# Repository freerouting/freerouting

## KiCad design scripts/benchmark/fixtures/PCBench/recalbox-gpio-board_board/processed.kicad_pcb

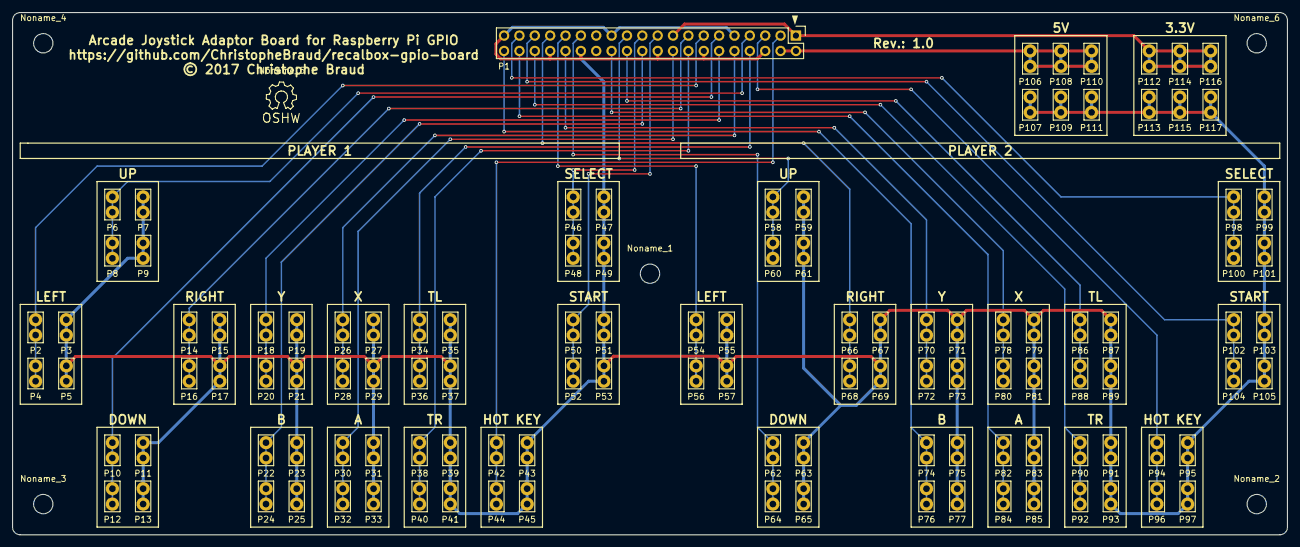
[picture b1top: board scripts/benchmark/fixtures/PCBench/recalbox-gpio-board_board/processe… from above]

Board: 2 copper layers, 210.8 x 86.4 mm, 123 parts (0 on the bottom side), 29 nets.

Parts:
Noname_1, Noname_2, Noname_3, Noname_4, Noname_6: MountingHole_3.2mm_M3
Noname_5: Symbol_OSHW-Logo_SilkScreen
P1: CONN_02X20; Pin_Header_Straight_2x20
P2, P4: <1; 61-3391-21
P3, P5, P7, P9, P11, P13, P15, P17, P19, P21, P23, P25, P27, P29, P31, P33, P35, P37, P39, P41, P43, P45, P47, P49, P51, P53, P55, P57, P59, P61, P63, P65, P67, P69, P71, P73, P75, P77, P79, P81, P83, P85, P87, P89, P91, P93, P95, P97, P99, P101, P103, P105, P107, P109, P111, P113, P115, P117: GND; 61-3391-21
P6, P8: 1; 61-3391-21
P10, P12: v1; 61-3391-21
P14, P16: >1; 61-3391-21
P18, P20: Y1; 61-3391-21
P22, P24: B1; 61-3391-21
P26, P28: X1; 61-3391-21
P30, P32: A1; 61-3391-21
P34, P36: TL1; 61-3391-21
P38, P40: TR1; 61-3391-21
P42, P44: HK1; 61-3391-21
P46, P48: SE1; 61-3391-21
P50, P52: ST1; 61-3391-21
P54, P56: <2; 61-3391-21
P58, P60: 2; 61-3391-21
P62, P64: v2; 61-3391-21
P66, P68: >2; 61-3391-21
P70, P72: Y2; 61-3391-21
P74, P76: B2; 61-3391-21
P78, P80: X2; 61-3391-21
P82, P84: A2; 61-3391-21
P86, P88: TL2; 61-3391-21
P90, P92: TR2; 61-3391-21
P94, P96: HK2; 61-3391-21
P98, P100: SE2; 61-3391-21
P102, P104: ST2; 61-3391-21
P106, P108, P110: 5V; 61-3391-21
P112, P114, P116: 3.3V; 61-3391-21

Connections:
+3V3: P1.1, P1.17, P112.1, P114.1, P116.1
+5V: P1.2, P1.4, P106.1, P108.1, P110.1
GND: P1.6, P1.9, P1.14, P1.20, P1.25, P1.30, P1.34, P1.39, P3.1, P5.1, P7.1, P9.1, P11.1, P13.1, P15.1, P17.1, P19.1, P21.1, P23.1, P25.1, P27.1, P29.1, P31.1, P33.1, P35.1, P37.1, P39.1, P41.1, P43.1, P45.1, P47.1, P49.1, P51.1, P53.1, P55.1, P57.1, P59.1, P61.1, P63.1, P65.1, P67.1, P69.1, P71.1, P73.1, P75.1, P77.1, P79.1, P81.1, P83.1, P85.1, P87.1, P89.1, P91.1, P93.1, P95.1, P97.1, P99.1, P101.1, P103.1, P105.1, P107.1, P109.1, P111.1, P113.1, P115.1, P117.1
unnamed: P1.3, P42.1, P44.1
unnamed: P1.5, P94.1, P96.1
unnamed: P1.7, P6.1, P8.1
unnamed: P1.8, P34.1, P36.1
unnamed: P1.10, P26.1, P28.1
unnamed: P1.11, P10.1, P12.1
unnamed: P1.12, P18.1, P20.1
unnamed: P1.13, P2.1, P4.1
unnamed: P1.15, P14.1, P16.1
unnamed: P1.16, P38.1, P40.1
unnamed: P1.18, P30.1, P32.1
unnamed: P1.19, P50.1, P52.1
unnamed: P1.21, P46.1, P48.1
unnamed: P1.22, P22.1, P24.1
unnamed: P1.23, P58.1, P60.1
unnamed: P1.24, P86.1, P88.1
unnamed: P1.26, P78.1, P80.1
unnamed: P1.29, P62.1, P64.1
unnamed: P1.31, P54.1, P56.1
unnamed: P1.32, P70.1, P72.1
unnamed: P1.33, P66.1, P68.1
unnamed: P1.35, P102.1, P104.1
unnamed: P1.36, P90.1, P92.1
unnamed: P1.37, P98.1, P100.1
unnamed: P1.38, P82.1, P84.1
unnamed: P1.40, P74.1, P76.1

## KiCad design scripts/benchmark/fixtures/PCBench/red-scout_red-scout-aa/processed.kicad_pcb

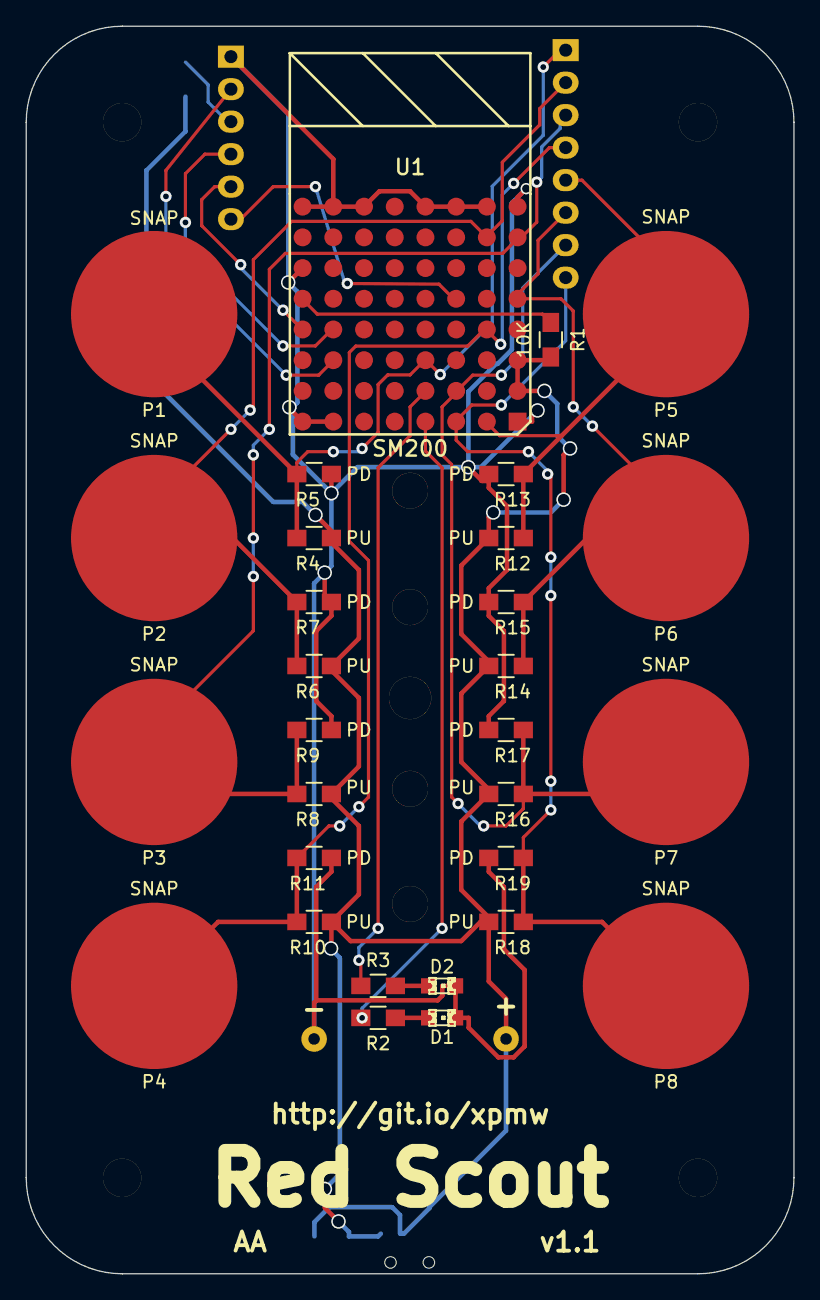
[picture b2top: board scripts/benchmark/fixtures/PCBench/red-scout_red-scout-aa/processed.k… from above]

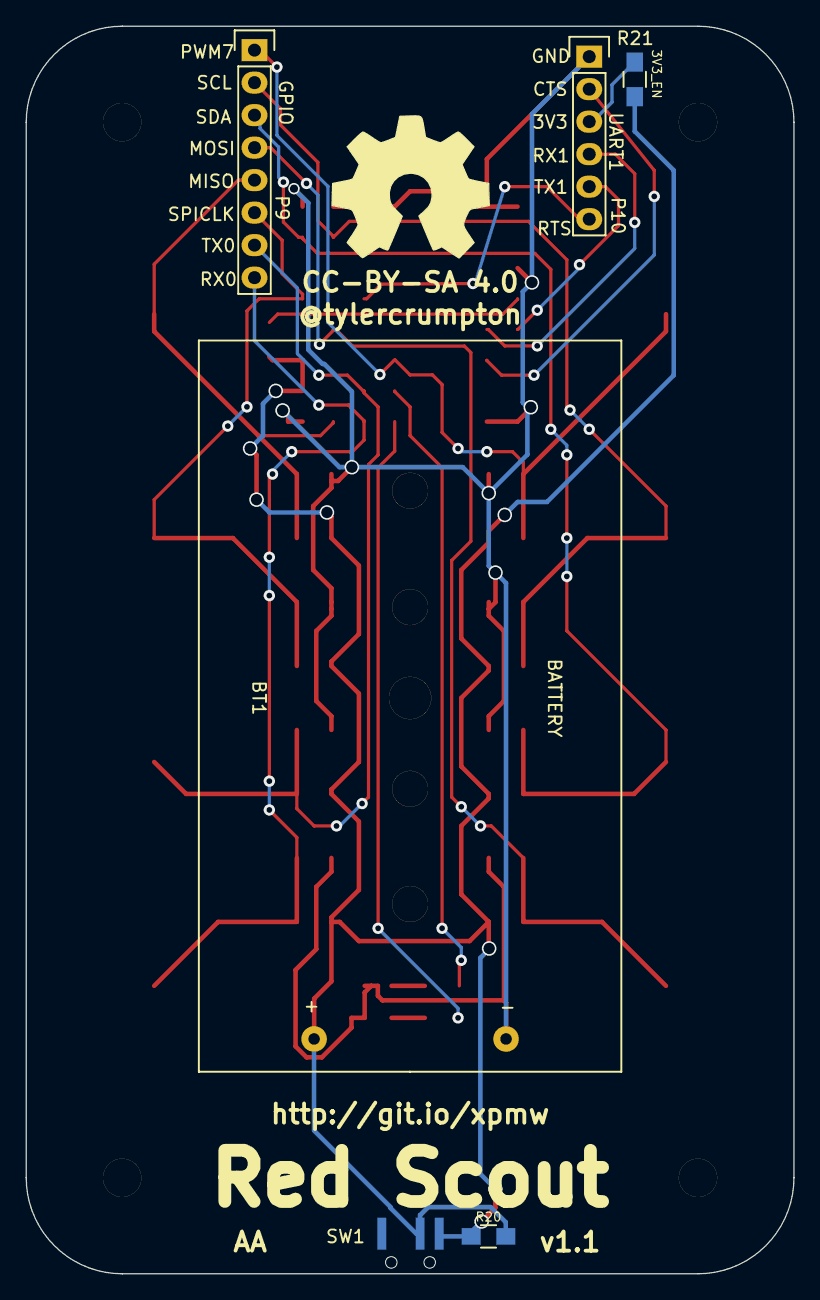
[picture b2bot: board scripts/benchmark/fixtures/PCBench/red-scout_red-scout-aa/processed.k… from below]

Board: 2 copper layers, 60.0 x 97.5 mm, 40 parts (6 on the bottom side), 21 nets.

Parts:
BT1: BATTERY; AA_battery_holder_12BH321P-GR
D1, D2: LED; LED-0805
MountingHole_3mm, MountingHole_3mm_2, MountingHole_3mm_3, MountingHole_3mm_4: VAL**; MountingHole_3mm
P1, P2, P3, P4, P5, P6, P7, P8: SNAP; 16_snap
P9: GPIO; Pin_Header_Straight_1x08
P10: UART1; Pin_Header_Straight_1x06
R1: 10K; R_0805_HandSoldering
R2, R3: 1K; R_0805_HandSoldering
R4, R6, R8, R10, R12, R14, R16, R18: PU; R_0805_HandSoldering
R5, R7, R9, R11, R13, R15, R17, R19: PD; R_0805_HandSoldering
R20: BYPASS; R_0805_HandSoldering
R21: 3V3_EN; R_0805_HandSoldering
SW1: SWITCH_INV; SPDT_slide_switch
U1: SM200

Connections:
CTS1: P10.2, U1.G3
GND: BT1.2, D1.2, D2.2, P10.1, R5.2, R7.2, R9.2, R11.2, R13.2, R15.2, R17.2, R19.2, U1.A1, U1.A8, U1.B8, U1.C8, U1.D8, U1.F8, U1.G1, U1.G8, U1.H1, U1.H6, U1.H8
MISO: P5.1, P9.5, R12.1, R13.1, U1.B1
MOSI: P4.1, P9.4, R10.1, R11.1, U1.B4
unnamed: BT1.1, R20.2, SW1.2
unnamed: D1.1, R2.2
unnamed: D2.1, R3.2
unnamed: P10.3, R21.1
unnamed: R1.1, U1.H5
PWM5: R2.1, U1.D1
PWM6: R3.1, U1.D2
PWM7: P1.1, P9.1, R4.1, R5.1, U1.D3
RTS1: P10.6, U1.C5
RX0: P8.1, P9.8, R18.1, R19.1, U1.C1
RX1: P10.4, U1.G4
SCL: P2.1, P9.2, R6.1, R7.1, U1.B7
SDA: P3.1, P9.3, R8.1, R9.1, U1.A7
SPICLK: P6.1, P9.6, R14.1, R15.1, U1.A5
TX0: P7.1, P9.7, R16.1, R17.1, U1.C2
TX1: P10.5, U1.H4
VCC: R1.2, R4.2, R6.2, R8.2, R10.2, R12.2, R14.2, R16.2, R18.2, R20.1, R21.2, SW1.3, U1.A2, U1.A3

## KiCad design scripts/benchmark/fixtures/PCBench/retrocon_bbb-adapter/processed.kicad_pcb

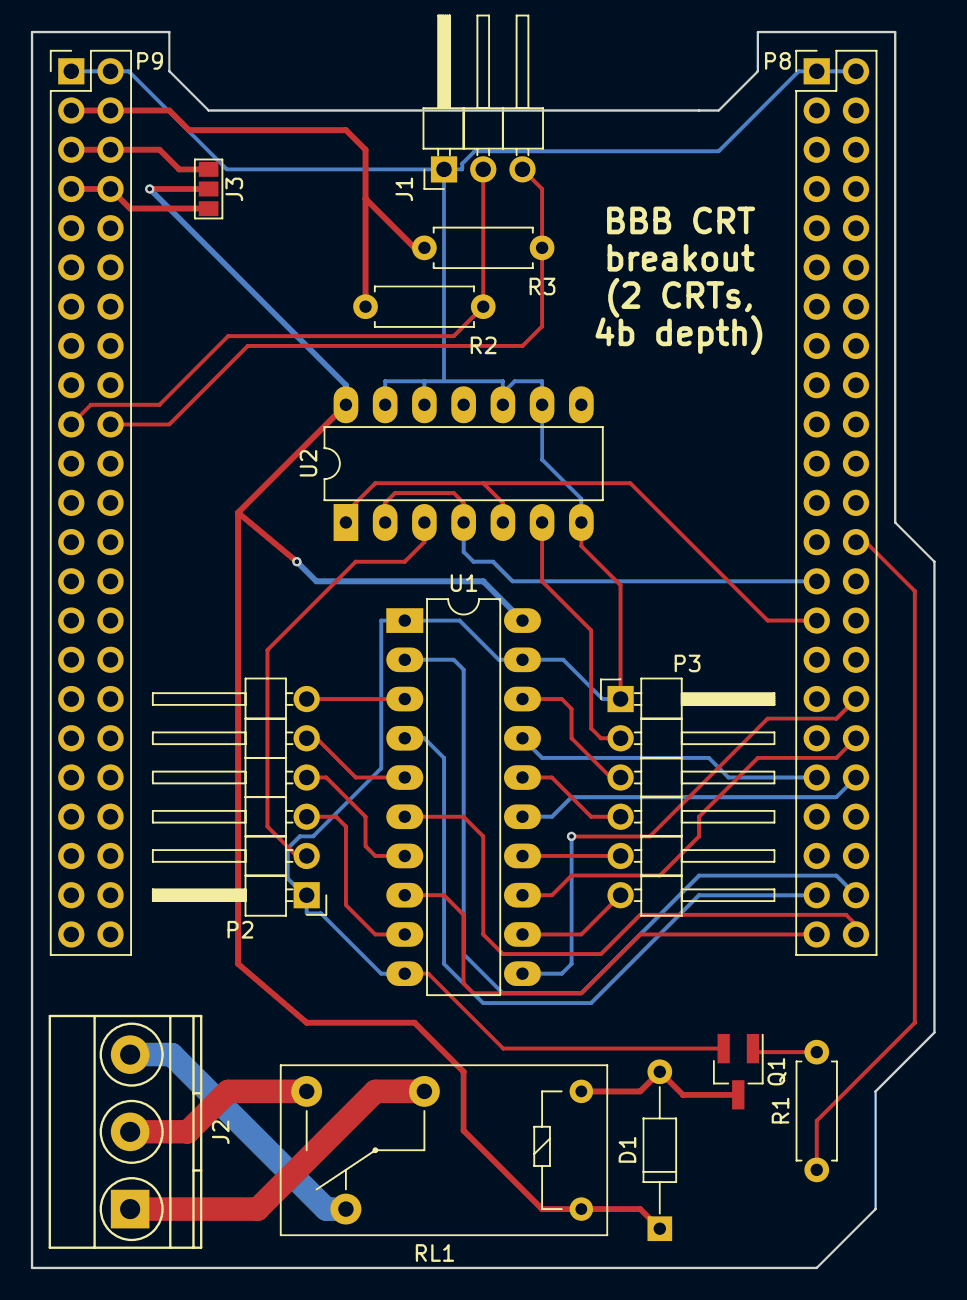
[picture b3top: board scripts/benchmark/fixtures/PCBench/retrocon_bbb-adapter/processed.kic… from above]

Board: 2 copper layers, 58.4 x 80.0 mm, 15 parts (0 on the bottom side), 33 nets.

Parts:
D1: 1N4148; D_DO-35_SOD27_P10.16mm_Horizontal
J1: CONN_01X03; Pin_Header_Angled_1x03_Pitch2.54mm
J2: Screw_Terminal_1x03; TerminalBlock_Pheonix_MKDS1.5-3pol
J3: GS3
P2, P3: CONN_01X06; Pin_Header_Angled_1x06_Pitch2.54mm
P8, P9: CONN_02X23; Pin_Header_Straight_2x23_Pitch2.54mm
Q1: Q_NMOS_GSD; SOT-23_Handsoldering
R1: 1K; R_Axial_DIN0207_L6.3mm_D2.5mm_P7.62mm_Horizontal
R2, R3: 4.7K; R_Axial_DIN0207_L6.3mm_D2.5mm_P7.62mm_Horizontal
RL1: G5Q-1; Relay_SPDT_OMRON-G5Q
U1: 74LS244; DIP-20_W7.62mm_LongPads
U2: 74LS32; DIP-14_W7.62mm_LongPads

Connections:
+3V3: P9.3, P9.4, R2.1, R3.1
BB_GPIO1_29: P8.26, R1.1
BB_HSYNC: P8.29, U2.1, U2.5
BB_I2C2_SCL: J1.2, P9.19, R2.2
BB_I2C2_SDA: J1.3, P9.20, R3.2
BB_LCD0: P8.45, U1.8
BB_LCD1: P8.46, U1.6
BB_LCD2: P8.43, U1.4
BB_LCD3: P8.44, U1.2
BB_LCD8: P8.37, U1.17
BB_LCD9: P8.38, U1.15
BB_LCD10: P8.36, U1.13
BB_LCD11: P8.34, U1.11
BB_VSYNC: P8.27, U2.2, U2.4
CSYNC_A: P3.2, U2.6
CSYNC_B: P2.2, U2.3
GND: J1.1, P2.1, P3.1, P8.1, P8.2, P9.1, P9.2, Q1.2, U1.1, U1.10, U1.19, U2.7, U2.9, U2.10, U2.12, U2.13
unnamed: D1.2, Q1.3, RL1.1
unnamed: J2.1, RL1.2
unnamed: J2.2, RL1.3
unnamed: J2.3, RL1.4
unnamed: P2.3, U1.9
unnamed: P2.4, U1.7
unnamed: P2.5, U1.5
unnamed: P2.6, U1.3
unnamed: P3.3, U1.18
unnamed: P3.4, U1.16
unnamed: P3.5, U1.14
unnamed: P3.6, U1.12
unnamed: Q1.1, R1.2
SYS_5V: J3.1, P9.7, P9.8
VCC: D1.1, J3.2, RL1.5, U1.20, U2.14
VDD_5V: J3.3, P9.5, P9.6

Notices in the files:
scripts/benchmark/fixtures/PCBench/recalbox-gpio-board_board/processed.kicad_pcb:
© 2017 Christophe Braud
scripts/benchmark/fixtures/PCBench/red-scout_red-scout-aa/processed.kicad_pcb:
CC-BY-SA 4.0
